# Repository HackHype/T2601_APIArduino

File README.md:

# T2601 — API Arduino
> Modular I/O expansion board based on the ATmega328PB.

---

## System Architecture

### 🟦 Main Board
_Mother board of the system — orchestrates the entire bus_

- Hosts a compact dev board (Teensy-style)
- **3 Mezzanine slots** for I/O interface cards
- **N System Mezzanine slots** for advanced modules
  - FRAM / RTC / MicroSD / ... modules
- Power management for the entire system

---

### 🟩 Extension Board
_Bus slave node — based on the ATmega328P_

- Microcontroller: **ATmega328P**
- **2 Mezzanine slots** for I/O
- **Chained UART** communication across all extension boards
- Programming via **Arduino as ISP**

---

### 🟨 Mezzanine Card
_swappable I/O interface module — 25 × 25 mm_

| Driver         | Type        | Typical Use                  |
|----------------|-------------|------------------------------|
| ULN2803        | Sink NPN    | Relays, inductive loads      |
| MIC2981        | Source PNP  | High-voltage loads           |
| MOSFET         | Switch      | Power loads                  |
| Voltage divider| Passive     | Analog input                 |
| Optocoupler    | Isolated    | Galvanic isolation           |

---

## Repository Structure
```
T2601_APIArduino/
├── hardware/
│   ├── main_board/        # Main board
│   ├── extension_board/   # ATmega328P extension board
│   └── mezzanine/         # I/O mezzanine cards
├── firmware/              # Arduino code
├── docs/                  # Schematics, datasheets
└── README.md
```

---

## License

This project is open hardware — **CERN OHL v2 Strongly Reciprocal**.

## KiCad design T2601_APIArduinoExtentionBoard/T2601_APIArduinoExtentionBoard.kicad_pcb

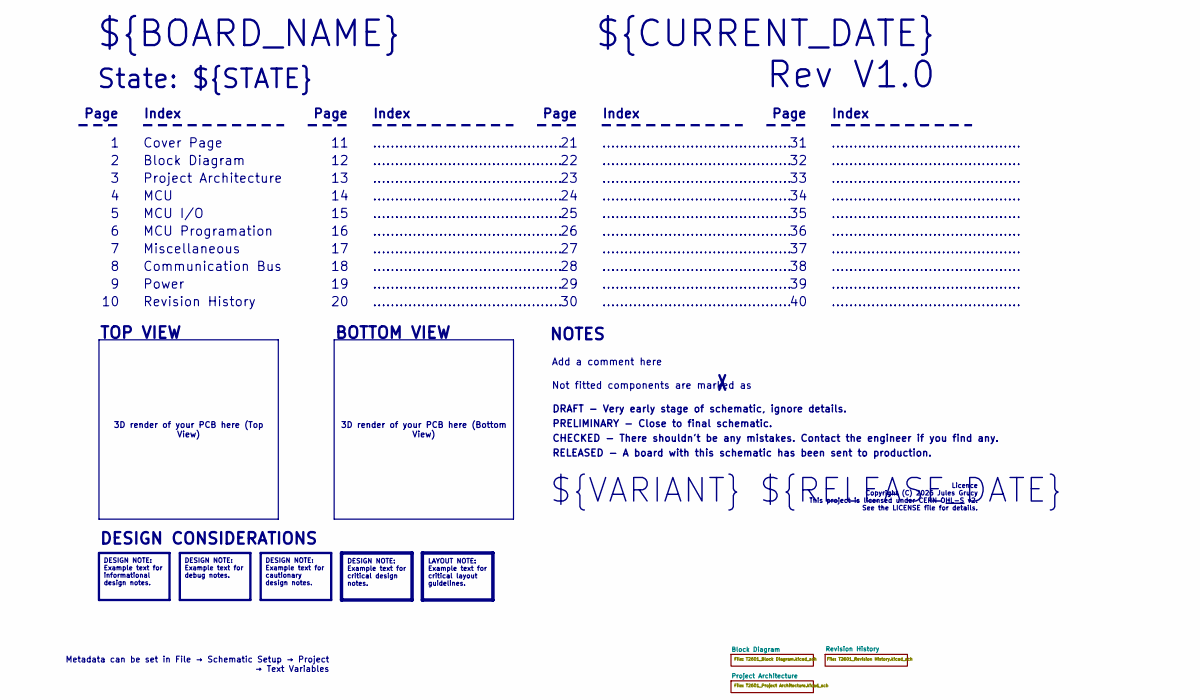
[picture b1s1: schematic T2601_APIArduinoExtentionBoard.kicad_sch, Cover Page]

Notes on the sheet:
BOTTOM VIEW
...........................................
RELEASED - A board with this schematic has been sent to production.
Page
TOP VIEW
Revision History
Power
Communication Bus
Not fitted components are marked as
Index
PRELIMINARY - Close to final schematic.
${VARIANT} ${RELEASE_DATE}
MCU
${CURRENT_DATE}
State: ${STATE}
Rev ${REVISION}
MCU I/O
${BOARD_NAME}
DRAFT - Very early stage of schematic, ignore details.
MCU Programation
Licence Copyright (C) 2026 Jules Grucy This project is licensed under CERN OHL-S v2. See the LICENSE file for details.
Block Diagram
Add a comment here
Cover Page
NOTES
Project Architecture
CHECKED - There shouldn't be any mistakes. Contact the engineer if you find any.
DESIGN CONSIDERATIONS
Miscellaneous
3D render of your PCB here (Bottom View)
3D render of your PCB here (Top View)
Metadata can be set in File → Schematic Setup → Project → Text Variables
DESIGN NOTE: Example text for informational design notes.
LAYOUT NOTE: Example text for critical layout guidelines.
DESIGN NOTE: Example text for cautionary design notes.
DESIGN NOTE: Example text for debug notes.
DESIGN NOTE: Example text for critical design notes.

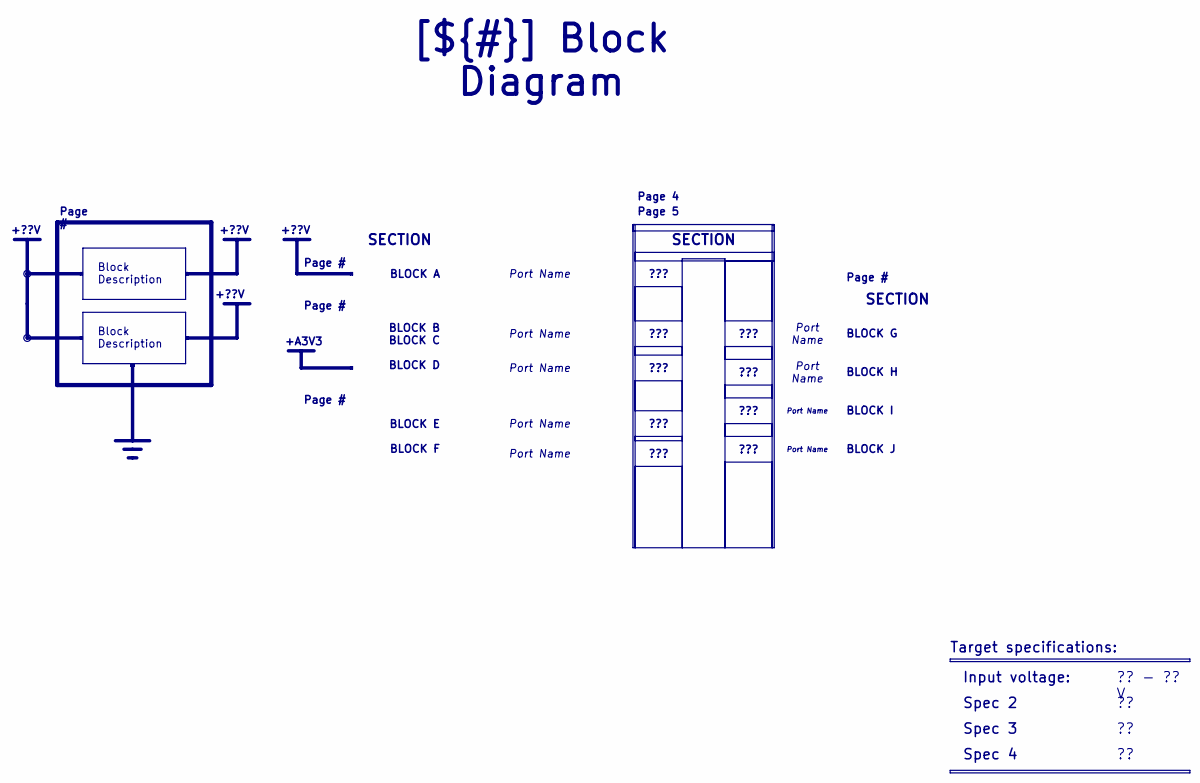
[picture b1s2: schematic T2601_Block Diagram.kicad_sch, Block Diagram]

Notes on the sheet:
+??V
+A3V3
Spec 3
Block Description
???
Spec 2
Port Name
SECTION
Page #
Input voltage:
BLOCK E BLOCK F
BLOCK A
BLOCK I
BLOCK G
[${#}] ${TITLE}
Target specifications:
?? - ?? V
Page 4
BLOCK J
Page 5
BLOCK B BLOCK C BLOCK D
Spec 4
BLOCK H

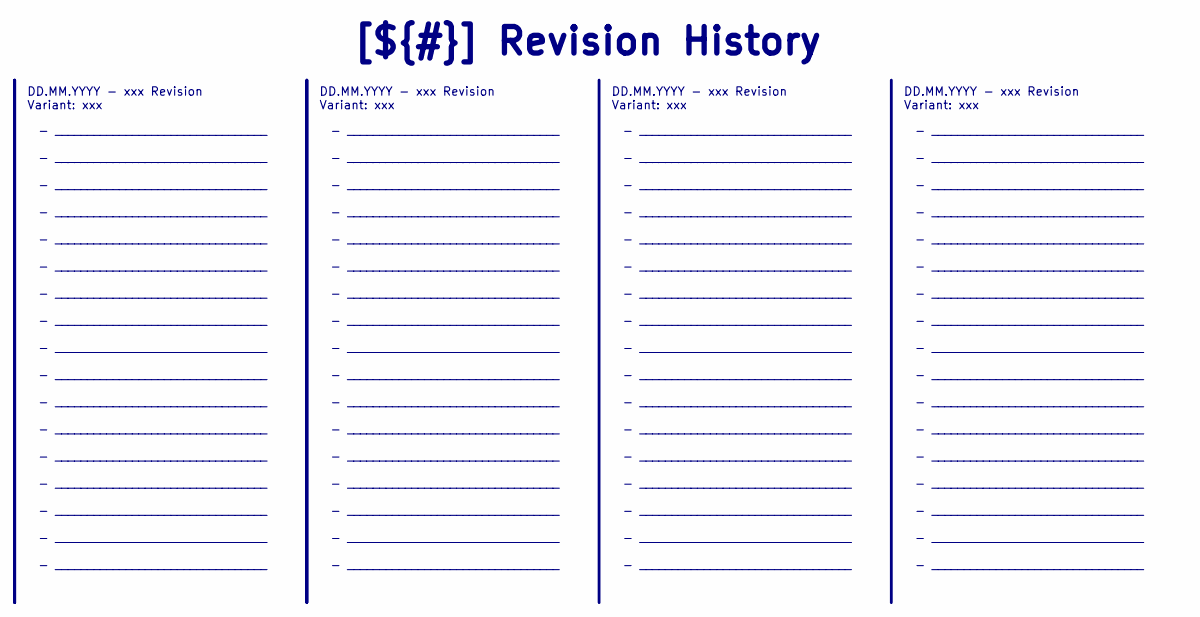
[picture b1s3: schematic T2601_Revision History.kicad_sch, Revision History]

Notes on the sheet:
- _________________________________ - _________________________________ - _________________________________ - _________________________________ - _________________________________ - _________________________________ - _________________________________ - _________________________________ - _________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
DD.MM.YYYY - xxx Revision Variant: xxx
[${#}] ${TITLE}

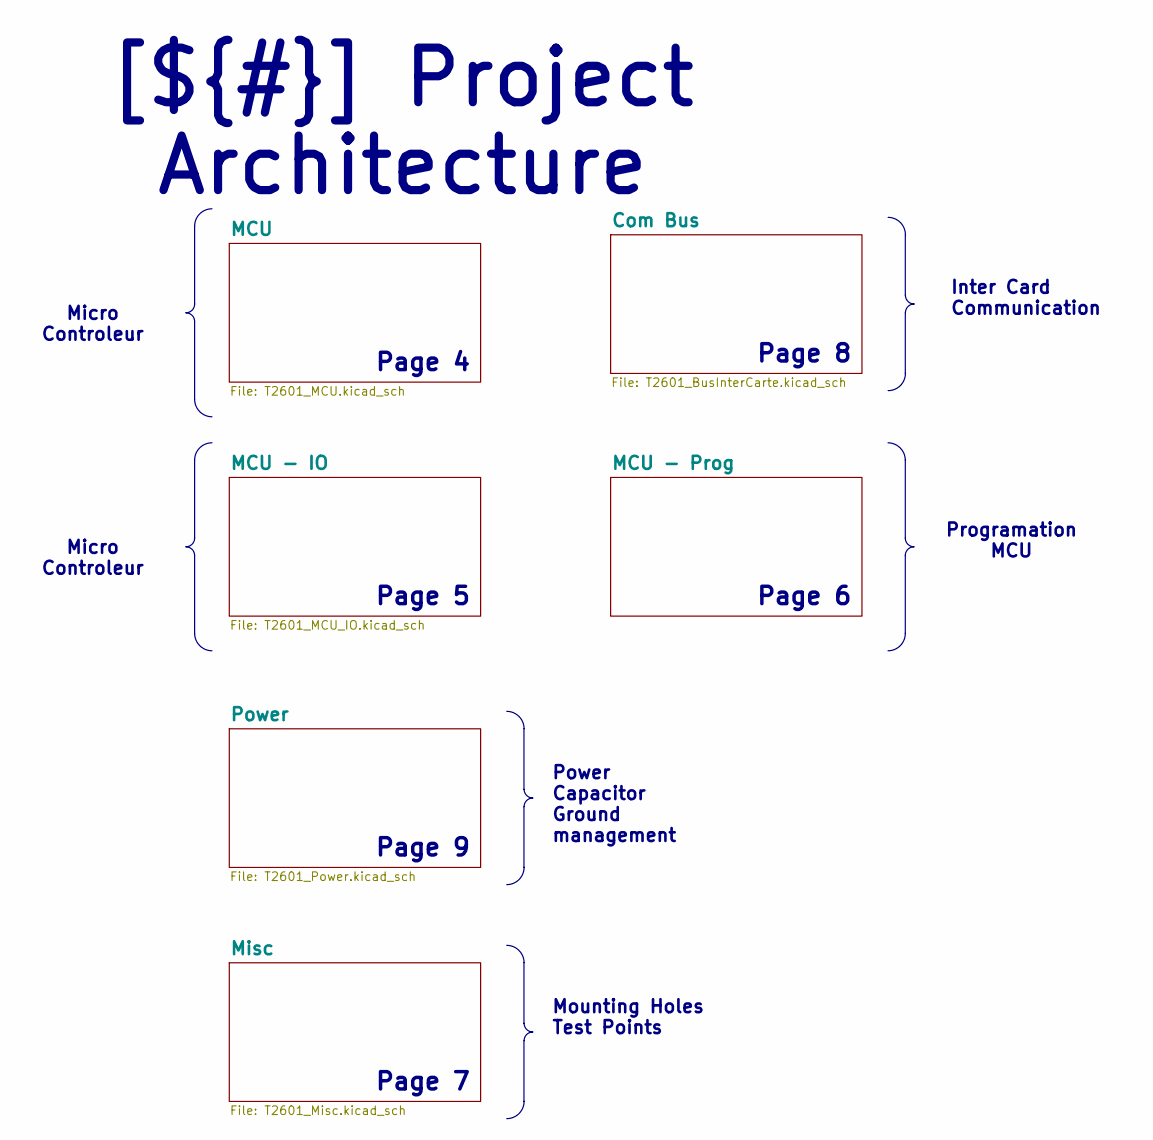
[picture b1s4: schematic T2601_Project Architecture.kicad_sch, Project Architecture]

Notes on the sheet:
Page 6
Page 8
Page 4
Page 5
Page 9
Page 7
Programation MCU
Micro Controleur
Inter Card Communication
[${#}] ${TITLE}
Power Capacitor Ground management
Mounting Holes Test Points

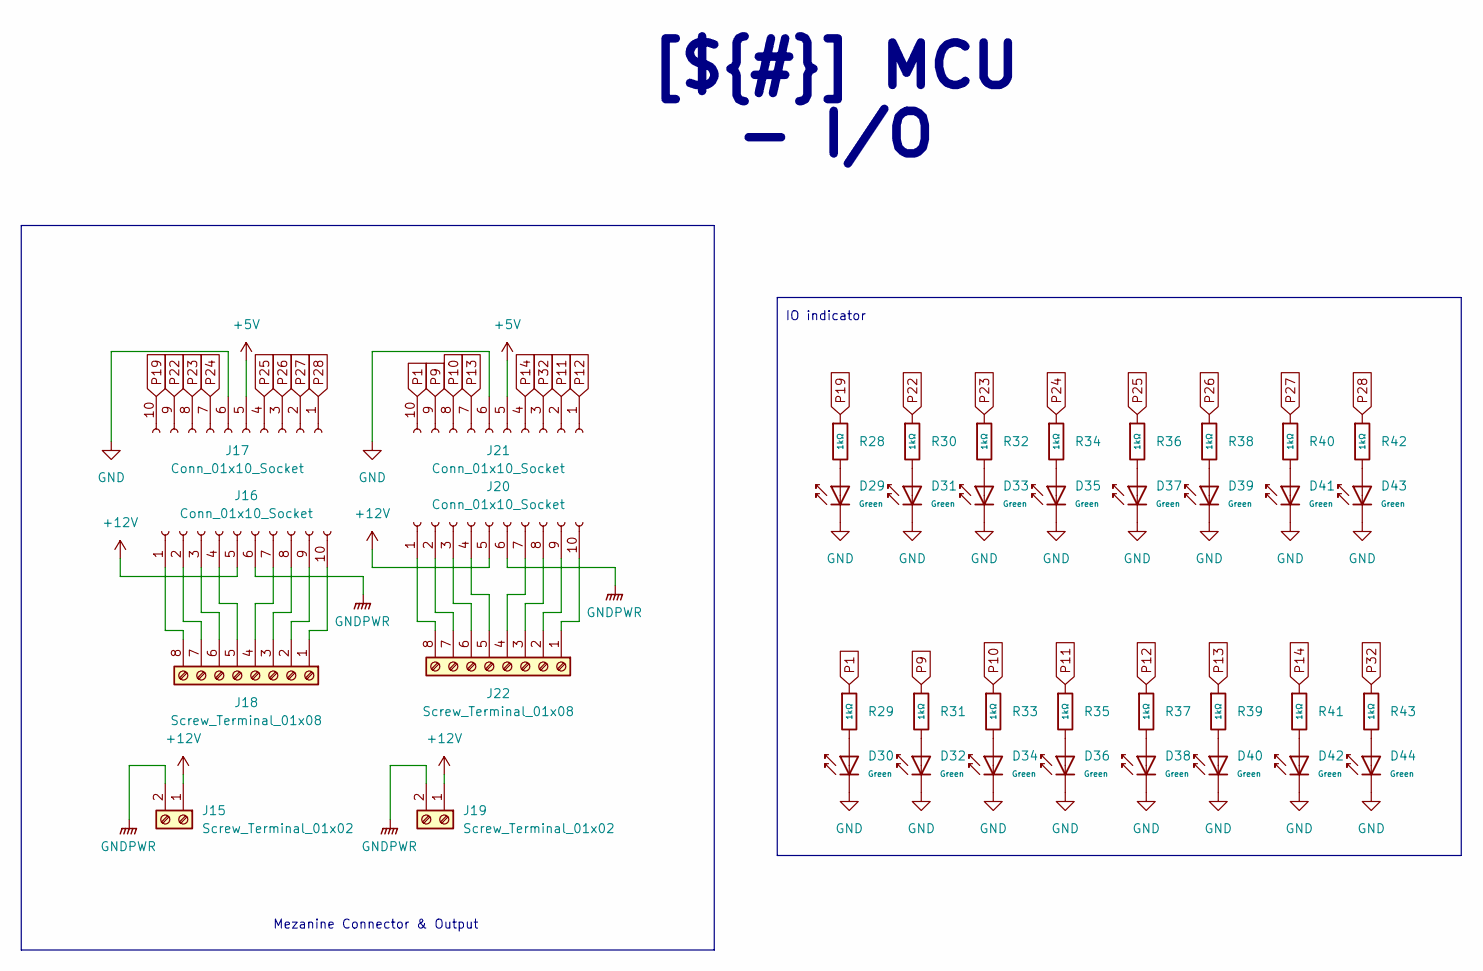
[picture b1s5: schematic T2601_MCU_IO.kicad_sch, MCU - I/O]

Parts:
D29, D30, D31, D32, D33, D34, D35, D36, D37, D38, D39, D40, D41, D42, D43, D44: Green; D_0805; Part KT-0805G; LCSC C2297
J15, J19: Screw_Terminal_01x02; TerminalBlock_Xinya_XY308-2.54-2P_1x02_P2.54mm_Horizontal
J16, J17, J20, J21: Conn_01x10_Socket; PinSocket_1x10_P2.54mm_Vertical
J18, J22: Screw_Terminal_01x08; TerminalBlock_TE_282834-8_1x08_P2.54mm_Horizontal
R28, R29, R30, R31, R32, R33, R34, R35, R36, R37, R38, R39, R40, R41, R42, R43: 1kΩ; R_0402; Overload Voltage (Max) 50V; Tolerance ±1%; Part 0402WGF1001TCE; LCSC C11702

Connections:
+5V: J17.5, J21.5; also elsewhere on the board
+12V: J15.1, J16.5, J19.1, J20.5; also elsewhere on the board
GND: D29.1, D30.1, D31.1, D32.1, D33.1, D34.1, D35.1, D36.1, D37.1, D38.1, D39.1, D40.1, D41.1, D42.1, D43.1, D44.1, J17.6, J21.6; also elsewhere on the board
GNDPWR: J15.2, J16.6, J19.2, J20.6; also elsewhere on the board
unnamed: D29.2, R28.2
unnamed: D30.2, R29.2
unnamed: D31.2, R30.2
unnamed: D32.2, R31.2
unnamed: D33.2, R32.2
unnamed: D34.2, R33.2
unnamed: D35.2, R34.2
unnamed: D36.2, R35.2
unnamed: D37.2, R36.2
unnamed: D38.2, R37.2
unnamed: D39.2, R38.2
unnamed: D40.2, R39.2
unnamed: D41.2, R40.2
unnamed: D42.2, R41.2
unnamed: D43.2, R42.2
unnamed: D44.2, R43.2
unnamed: J16.1, J18.8
unnamed: J16.2, J18.7
unnamed: J16.3, J18.6
unnamed: J16.4, J18.5
unnamed: J16.7, J18.4
unnamed: J16.8, J18.3
unnamed: J16.9, J18.2
unnamed: J16.10, J18.1
unnamed: J20.1, J22.8
unnamed: J20.2, J22.7
unnamed: J20.3, J22.6
unnamed: J20.4, J22.5
unnamed: J20.7, J22.4
unnamed: J20.8, J22.3
unnamed: J20.9, J22.2
unnamed: J20.10, J22.1
P1: J21.10, R29.1; also elsewhere on the board
P9: J21.9, R31.1; also elsewhere on the board
P10: J21.8, R33.1; also elsewhere on the board
P11: J21.2, R35.1; also elsewhere on the board
P12: J21.1, R37.1; also elsewhere on the board
P13: J21.7, R39.1; also elsewhere on the board
P14: J21.4, R41.1; also elsewhere on the board
P19: J17.10, R28.1; also elsewhere on the board
P22: J17.9, R30.1; also elsewhere on the board
P23: J17.8, R32.1; also elsewhere on the board
P24: J17.7, R34.1; also elsewhere on the board
P25: J17.4, R36.1; also elsewhere on the board
P26: J17.3, R38.1; also elsewhere on the board
P27: J17.2, R40.1; also elsewhere on the board
P28: J17.1, R42.1; also elsewhere on the board
P32: J21.3, R43.1; also elsewhere on the board

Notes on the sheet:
IO indicator
Mezanine Connector & Output
[${#}] ${TITLE}

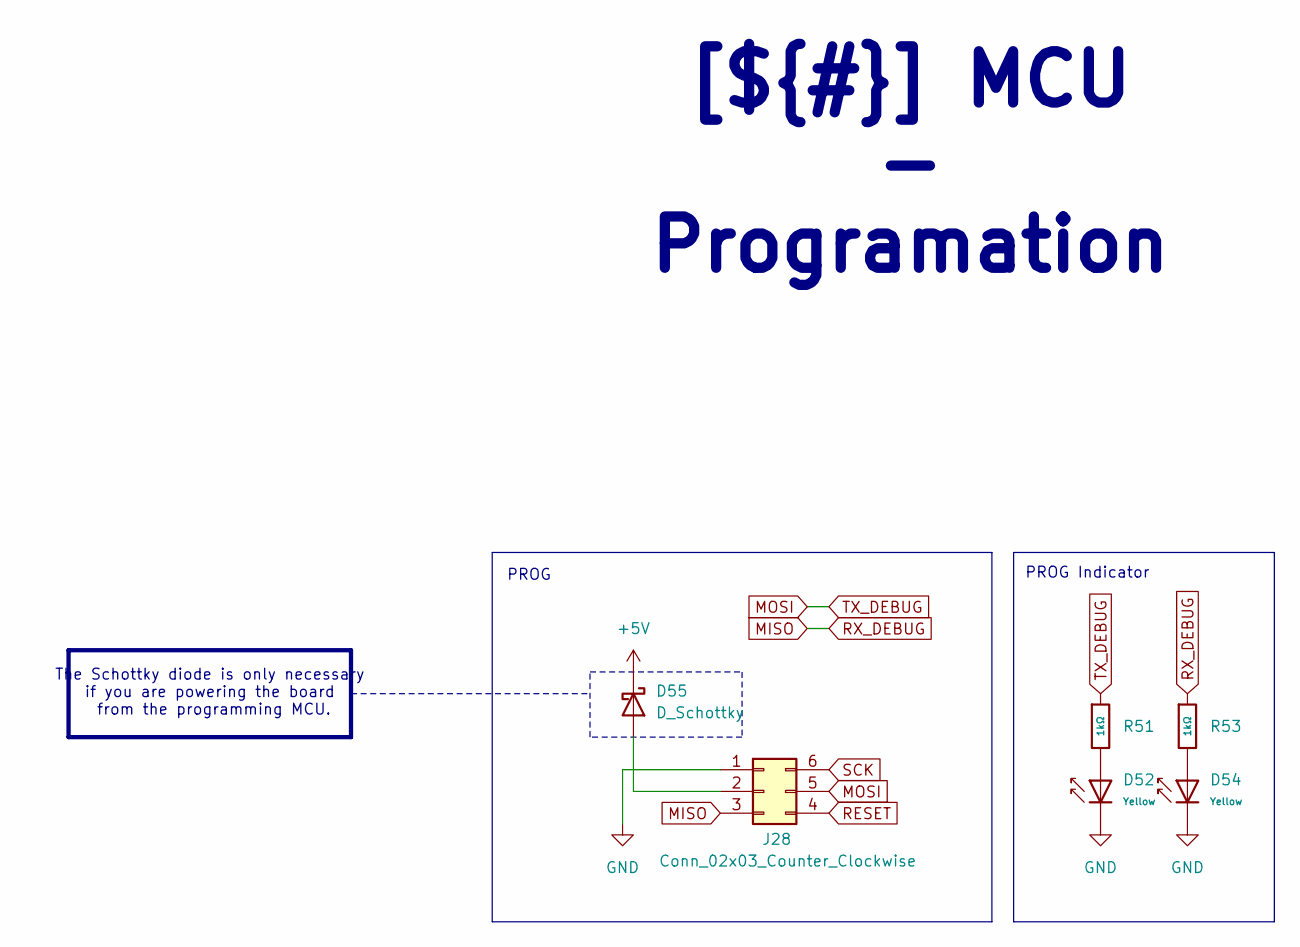
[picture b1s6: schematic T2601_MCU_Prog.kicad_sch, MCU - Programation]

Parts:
D52, D54: Yellow; D_0805; Part KT-0805Y; LCSC C2296
D55: D_Schottky; D_5W_P12.70mm_Horizontal
J28: Conn_02x03_Counter_Clockwise; PinSocket_2x03_P2.54mm_Vertical
R51, R53: 1kΩ; R_0402; Overload Voltage (Max) 50V; Tolerance ±1%; Part 0402WGF1001TCE; LCSC C11702

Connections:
+5V: D55.1 (K); also elsewhere on the board
GND: D52.1, D54.1, J28.1; also elsewhere on the board
MISO: J28.3, R53.1; also elsewhere on the board
MOSI: J28.5, R51.1; also elsewhere on the board
unnamed: D52.2, R51.2
unnamed: D54.2, R53.2
unnamed: D55.2 (A), J28.2
RESET: J28.4; also elsewhere on the board
SCK: J28.6; also elsewhere on the board

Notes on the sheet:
PROG Indicator
PROG
The Schottky diode is only necessary if you are powering the board from the programming MCU.
[${#}] ${TITLE}

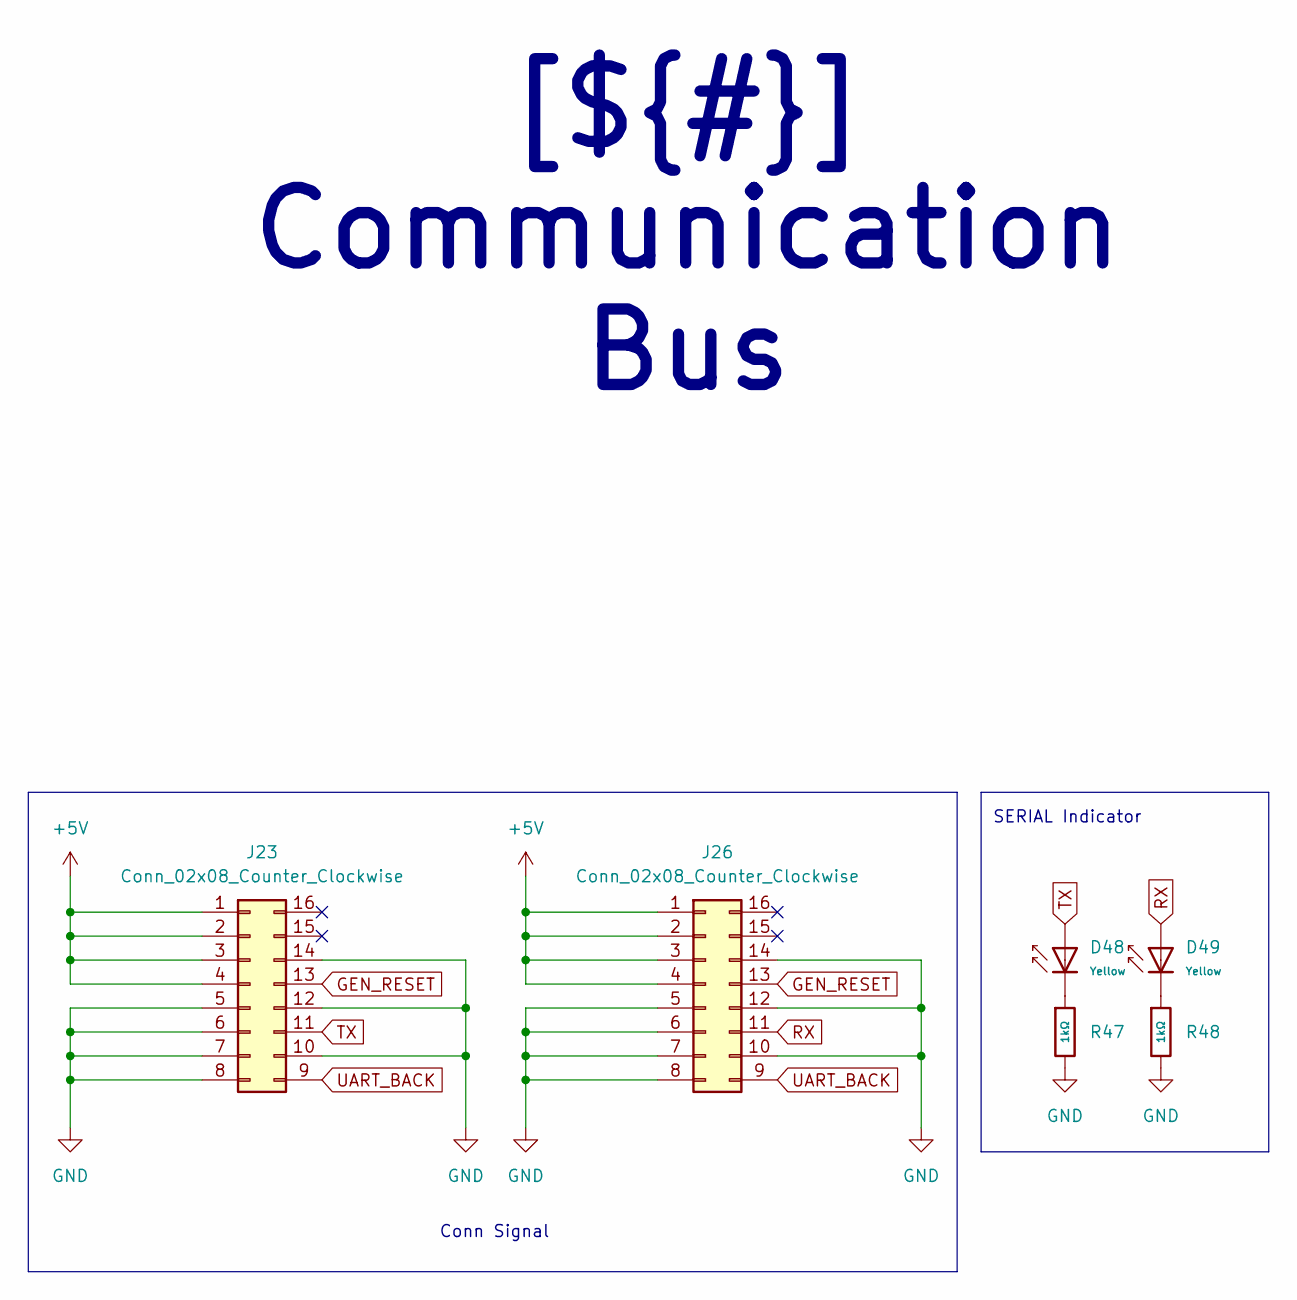
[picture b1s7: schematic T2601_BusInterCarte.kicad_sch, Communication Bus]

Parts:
D48, D49: Yellow; D_0805; Part KT-0805Y; LCSC C2296
J23, J26: Conn_02x08_Counter_Clockwise; IDC-Header_2x08_P2.54mm_Vertical
R47, R48: 1kΩ; R_0402; Overload Voltage (Max) 50V; Tolerance ±1%; Part 0402WGF1001TCE; LCSC C11702

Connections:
+5V: J23.1, J23.2, J23.3, J23.4, J26.1, J26.2, J26.3, J26.4; also elsewhere on the board
GEN_RESET: J23.13, J26.13; also elsewhere on the board
GND: J23.5, J23.6, J23.7, J23.8, J23.10, J23.12, J23.14, J26.5, J26.6, J26.7, J26.8, J26.10, J26.12, J26.14, R47.2, R48.2; also elsewhere on the board
unnamed: D48.1, R47.1
unnamed: D49.1, R48.1
RX: D49.2, J26.11; also elsewhere on the board
TX: D48.2, J23.11; also elsewhere on the board
UART_BACK: J23.9, J26.9

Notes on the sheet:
Conn Signal
SERIAL Indicator
[${#}] ${TITLE}

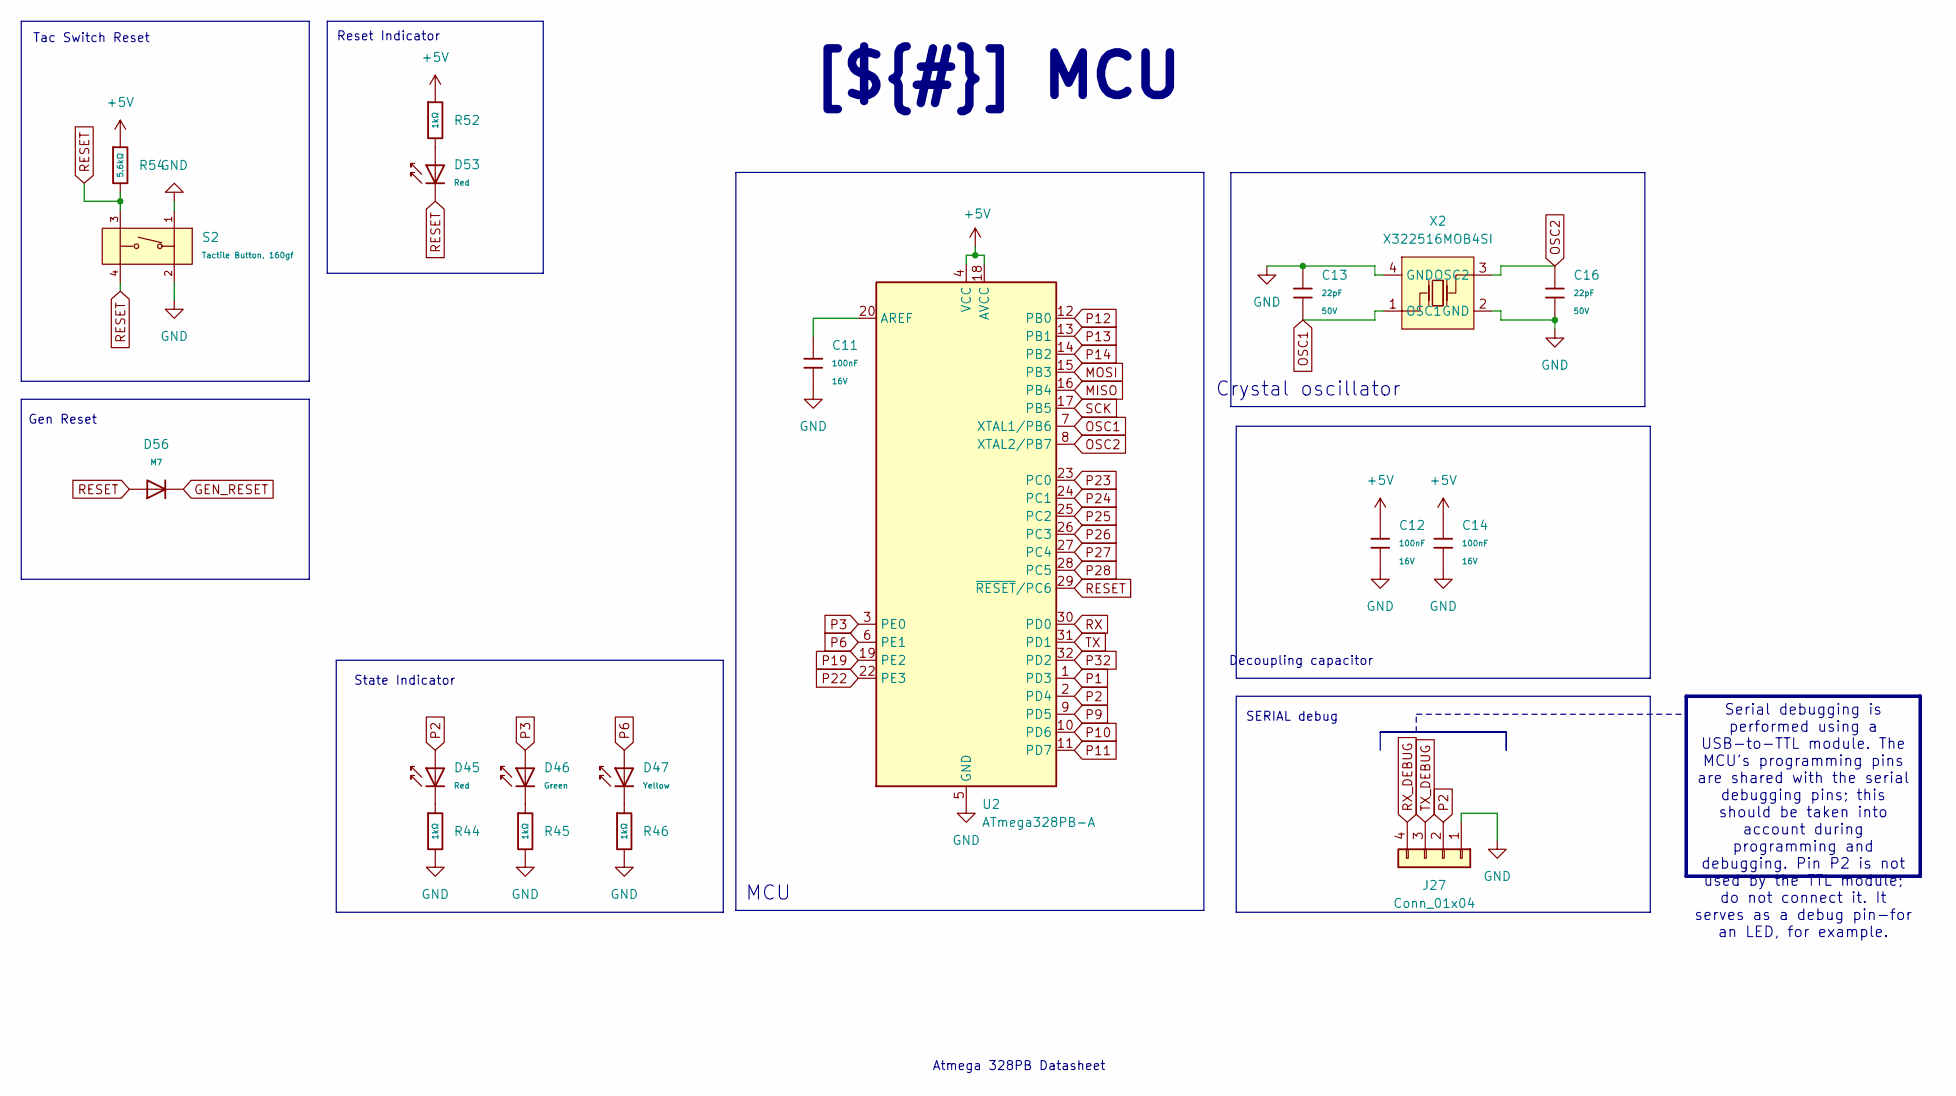
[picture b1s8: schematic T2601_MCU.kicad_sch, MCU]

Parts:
C11, C12, C14: 100nF; C_0402; Voltage Rated 16V; Tolerance ±10%; Part CL05B104KO5NNNC; LCSC C1525
C13, C16: 22pF; C_0402; Voltage Rated 50V; Tolerance ±5%; Part 0402CG220J500NT; LCSC C1555
D45, D53: Red; D_0805; Forward Voltage (VF) 1.6V~2.6V; Part NCD0805R1; LCSC C84256
D46: Green; D_0805; Part KT-0805G; LCSC C2297
D47: Yellow; D_0805; Part KT-0805Y; LCSC C2296
D56: M7; D_SMA; Forward Voltage (Vf@If) 1.1V@1A; Reverse Voltage (Vr) 1kV; Part M7; LCSC C95872
J27: Conn_01x04; PinSocket_1x04_P2.54mm_Vertical
R44, R45, R46, R52: 1kΩ; R_0402; Overload Voltage (Max) 50V; Tolerance ±1%; Part 0402WGF1001TCE; LCSC C11702
R54: 5.6kΩ; R_0603; Overload Voltage (Max) 75V; Tolerance ±1%; Part 0603WAF5601T5E; LCSC C23189
S2: Tactile Button, 160gf; SW-SMD_4P-L5.1-W5.1-P3.70-LS6.5-TL-2; Voltage Rating (Dc) 12V; Part TS-1187A-B-A-B; LCSC C318884
U2: ATmega328PB-A; TQFP-32_7x7mm_P0.8mm
X2: X322516MOB4SI; CRYSTAL-SMD_4P-L3.2-W2.5-BL; LCSC Part C12668

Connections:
+5V: C12.1, C14.1, R52.1, R54.1, U2.4 (VCC), U2.18 (AVCC); also elsewhere on the board
GEN_RESET: D56.1; also elsewhere on the board
GND: C11.2, C12.2, C13.1, C14.2, C16.2, J27.1, R44.2, R45.2, R46.2, S2.1 (A), S2.2 (B), U2.5 (GND), U2.21 (GND), X2.2 (GND), X2.4 (GND); also elsewhere on the board
MISO: J27.4, U2.16 (PB4); also elsewhere on the board
MOSI: J27.3, U2.15 (PB3); also elsewhere on the board
unnamed: D45.1, R44.1
unnamed: D46.1, R45.1
unnamed: D47.1, R46.1
unnamed: D53.2, R52.2
unnamed: C11.1, U2.20 (AREF)
OSC1: C13.2, U2.7 (XTAL1/PB6), X2.1 (OSC1)
OSC2: C16.1, U2.8 (XTAL2/PB7), X2.3 (OSC2)
P1: U2.1 (PD3); also elsewhere on the board
P2: D45.2, J27.2, U2.2 (PD4)
P3: D46.2, U2.3 (PE0)
P6: D47.2, U2.6 (PE1)
P9: U2.9 (PD5); also elsewhere on the board
P10: U2.10 (PD6); also elsewhere on the board
P11: U2.11 (PD7); also elsewhere on the board
P12: U2.12 (PB0); also elsewhere on the board
P13: U2.13 (PB1); also elsewhere on the board
P14: U2.14 (PB2); also elsewhere on the board
P19: U2.19 (PE2); also elsewhere on the board
P22: U2.22 (PE3); also elsewhere on the board
P23: U2.23 (PC0); also elsewhere on the board
P24: U2.24 (PC1); also elsewhere on the board
P25: U2.25 (PC2); also elsewhere on the board
P26: U2.26 (PC3); also elsewhere on the board
P27: U2.27 (PC4); also elsewhere on the board
P28: U2.28 (PC5); also elsewhere on the board
P32: U2.32 (PD2); also elsewhere on the board
RESET: D53.1, D56.2, R54.2, S2.3 (C), S2.4 (D), U2.29 (~RESET/PC6); also elsewhere on the board
RX: U2.30 (PD0); also elsewhere on the board
SCK: U2.17 (PB5); also elsewhere on the board
TX: U2.31 (PD1); also elsewhere on the board

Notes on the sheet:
State Indicator
Decoupling capacitor
Tac Switch Reset
Gen Reset
MCU
SERIAL debug
Atmega 328PB Datasheet
Crystal oscillator
Reset Indicator
Serial debugging is performed using a USB-to-TTL module. The MCU's programming pins are shared with the serial debugging pins; this should be taken into account during programming and debugging. Pin P2 is not used by the TTL module; do not connect it. It serves as a debug pin-for an LED, for exampl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
[${#}] ${TITLE}

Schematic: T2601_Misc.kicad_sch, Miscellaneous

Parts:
H1, H2, H3, H4: MountingHole; MountingHole_3.2mm_M3
TP1, TP2, TP3: TestPoint; TestPoint_Loop_D2.50mm_Drill1.0mm_LowProfile

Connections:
+5V: TP3.1 (1_1); also elsewhere on the board
+12V: TP2.1 (1_1); also elsewhere on the board
GND: TP1.1 (1_1); also elsewhere on the board

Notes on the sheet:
[${#}] ${TITLE}

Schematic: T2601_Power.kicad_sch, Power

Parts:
C9, C10: C; C_Radial_D6.3mm_H11.0mm_P2.50mm
D50, D51: Green; D_0805; Part KT-0805G; LCSC C2297
J24, J25: Conn_01x04_Pin; JST_XH_B4B-XH-A_1x04_P2.50mm_Vertical
JP13, JP14, JP16, JP17, JP18, JP20, JP21, JP22, JP24: SolderJumper_2_Open; SolderJumper-2_P1.3mm_Open_RoundedPad1.0x1.5mm
R49: 2.4kΩ; R_0603; Overload Voltage (Max) 75V; Tolerance ±1%; Part 0603WAF2401T5E; LCSC C22940
R50: 1kΩ; R_0603; Overload Voltage (Max) 75V; Tolerance ±1%; Part 0603WAF1001T5E; LCSC C21190

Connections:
+5V: C9.1, C10.1, R50.1; also elsewhere on the board
+12V: J24.3, J24.4, J25.3, J25.4, R49.1; also elsewhere on the board
GND: C9.2, C10.2, D51.1, JP13.1 (A), JP14.1 (A), JP16.1 (A), JP17.1 (A), JP18.1 (A), JP20.1 (A), JP21.1 (A), JP22.1 (A), JP24.1 (A); also elsewhere on the board
GNDPWR: D50.1, J24.1, J24.2, J25.1, J25.2, JP13.2 (B), JP14.2 (B), JP16.2 (B), JP17.2 (B), JP18.2 (B), JP20.2 (B), JP21.2 (B), JP22.2 (B), JP24.2 (B); also elsewhere on the board
unnamed: D50.2, R49.2
unnamed: D51.2, R50.2

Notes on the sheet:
PWR Indicator
Conn PWR
[${#}] ${TITLE}

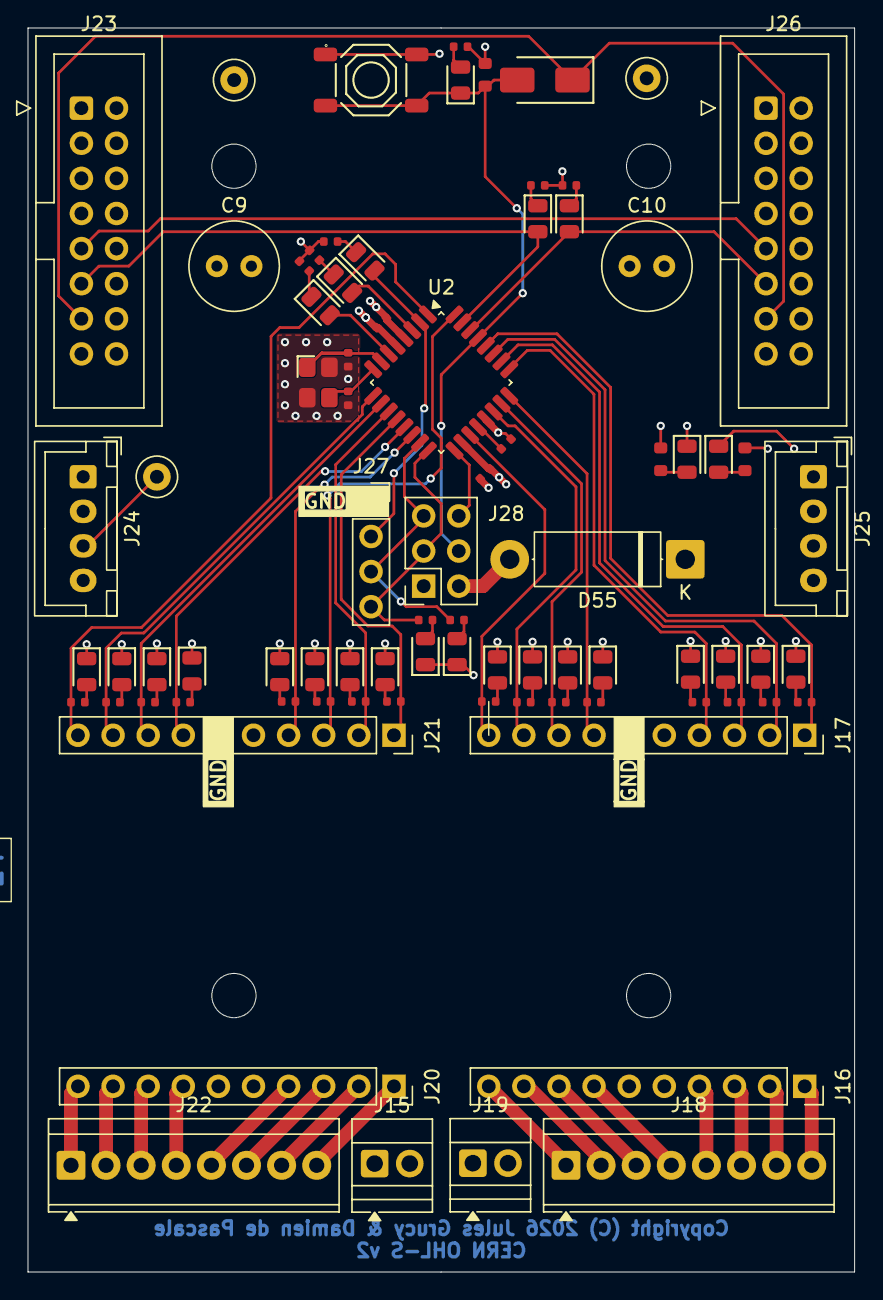
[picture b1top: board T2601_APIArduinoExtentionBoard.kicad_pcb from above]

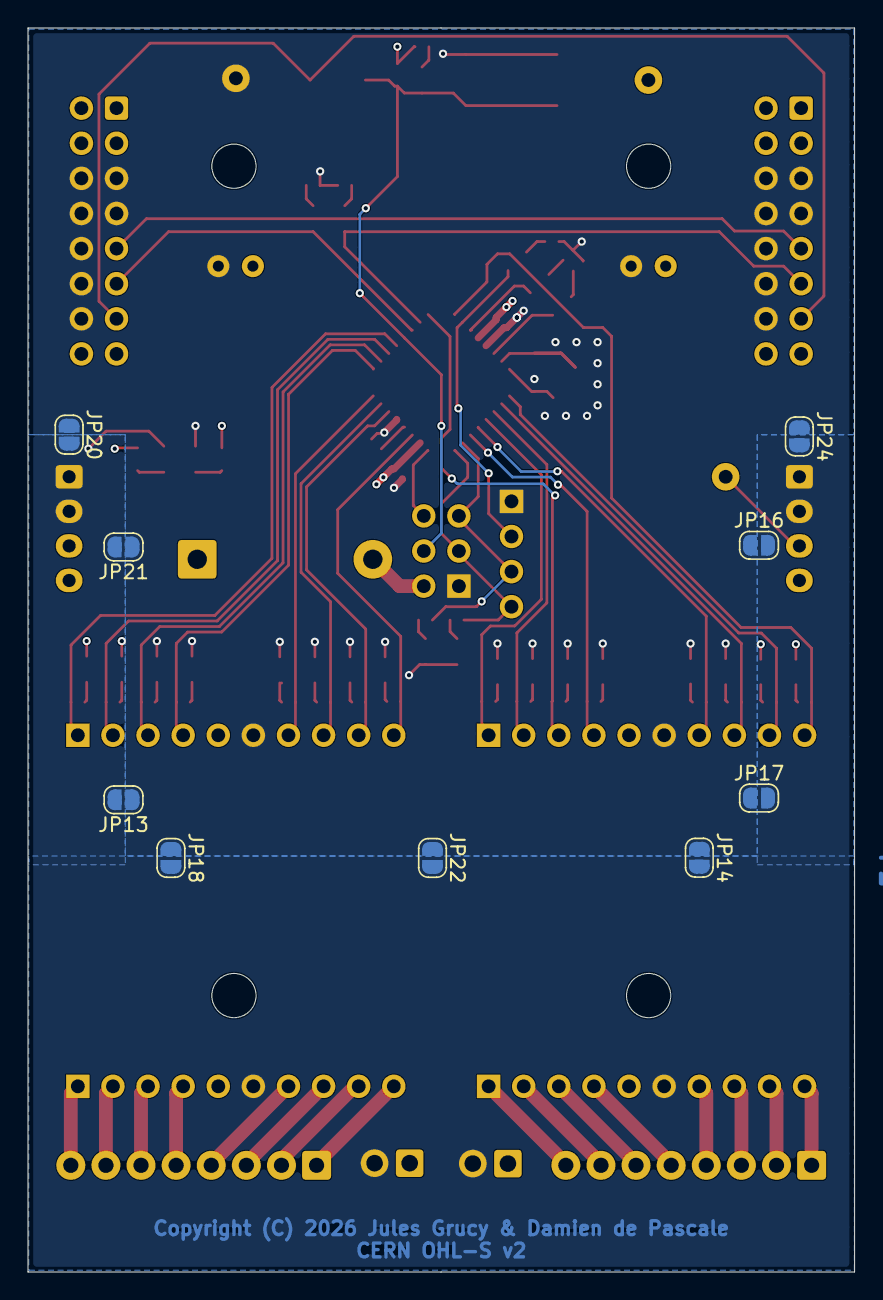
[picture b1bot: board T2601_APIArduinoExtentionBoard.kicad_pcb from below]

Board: 4 copper layers, 59.8 x 90.0 mm, 95 parts (9 on the bottom side), 77 nets.

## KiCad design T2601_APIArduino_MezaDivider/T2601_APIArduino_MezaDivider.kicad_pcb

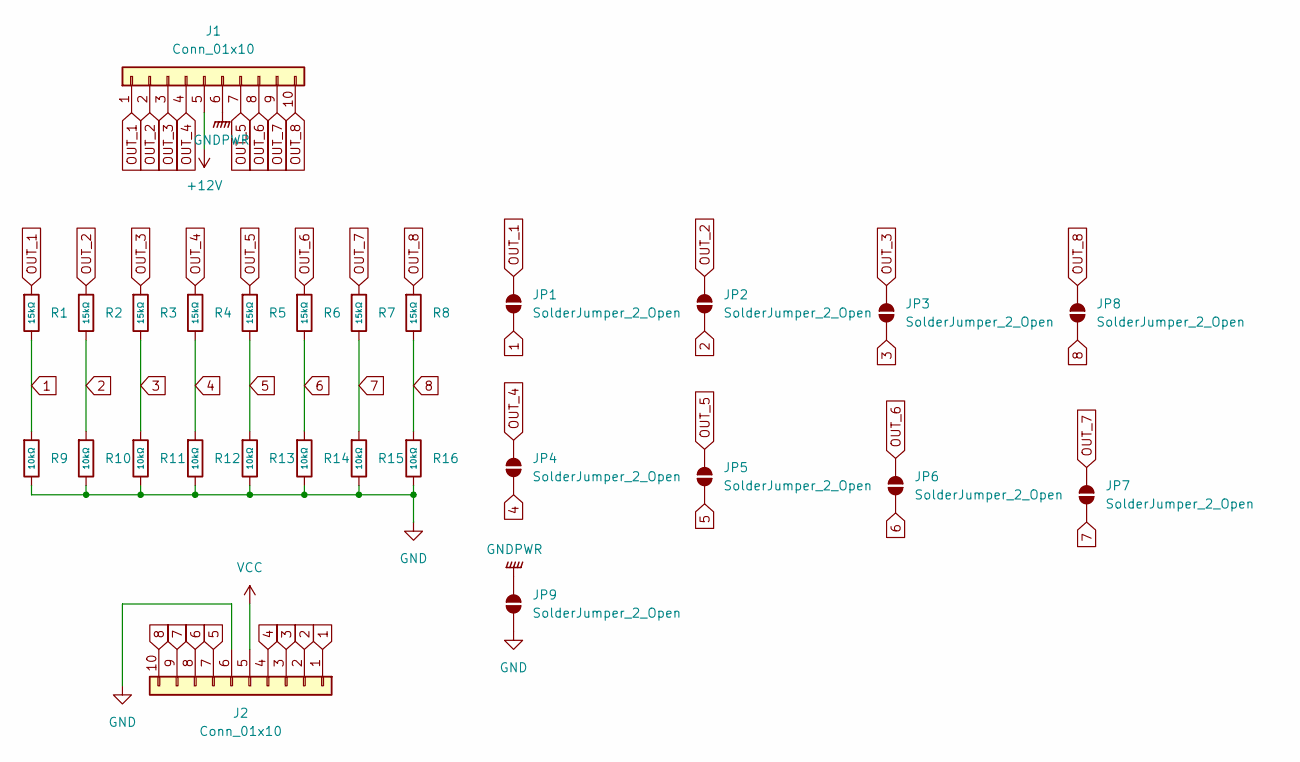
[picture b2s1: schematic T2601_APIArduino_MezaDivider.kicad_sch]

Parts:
J1, J2: Conn_01x10; PinHeader_1x10_P2.54mm_Vertical
JP1, JP2, JP3, JP4, JP5, JP6, JP7, JP8, JP9: SolderJumper_2_Open; SolderJumper-2_P1.3mm_Open_RoundedPad1.0x1.5mm
R1, R2, R3, R4, R5, R6, R7, R8: 15kΩ; R_0402; Overload Voltage (Max) 50V; Tolerance ±1%; Part 0402WGF1502TCE; LCSC C25756
R9, R10, R11, R12, R13, R14, R15, R16: 10kΩ; R_0402; Overload Voltage (Max) 50V; Tolerance ±1%; Part 0402WGF1002TCE; LCSC C25744

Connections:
1: J2.1, JP1.1 (A), R1.2, R9.1
2: J2.2, JP2.1 (A), R2.2, R10.1
3: J2.3, JP3.1 (A), R3.2, R11.1
4: J2.4, JP4.1 (A), R4.2, R12.1
5: J2.7, JP5.1 (A), R5.2, R13.1
6: J2.8, JP6.1 (A), R6.2, R14.1
7: J2.9, JP7.1 (A), R7.2, R15.1
8: J2.10, JP8.1 (A), R8.2, R16.1
+12V: J1.5
GND: J2.6, JP9.1 (A), R9.2, R10.2, R11.2, R12.2, R13.2, R14.2, R15.2, R16.2
GNDPWR: J1.6, JP9.2 (B)
OUT_1: J1.1, JP1.2 (B), R1.1
OUT_2: J1.2, JP2.2 (B), R2.1
OUT_3: J1.3, JP3.2 (B), R3.1
OUT_4: J1.4, JP4.2 (B), R4.1
OUT_5: J1.7, JP5.2 (B), R5.1
OUT_6: J1.8, JP6.2 (B), R6.1
OUT_7: J1.9, JP7.2 (B), R7.1
OUT_8: J1.10, JP8.2 (B), R8.1
VCC: J2.5

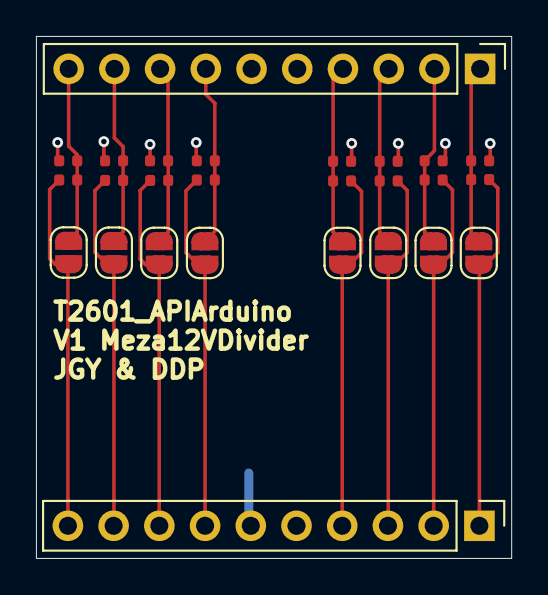
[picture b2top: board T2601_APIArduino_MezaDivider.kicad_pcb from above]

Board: 2 copper layers, 26.4 x 29.0 mm, 27 parts (1 on the bottom side), 18 nets.

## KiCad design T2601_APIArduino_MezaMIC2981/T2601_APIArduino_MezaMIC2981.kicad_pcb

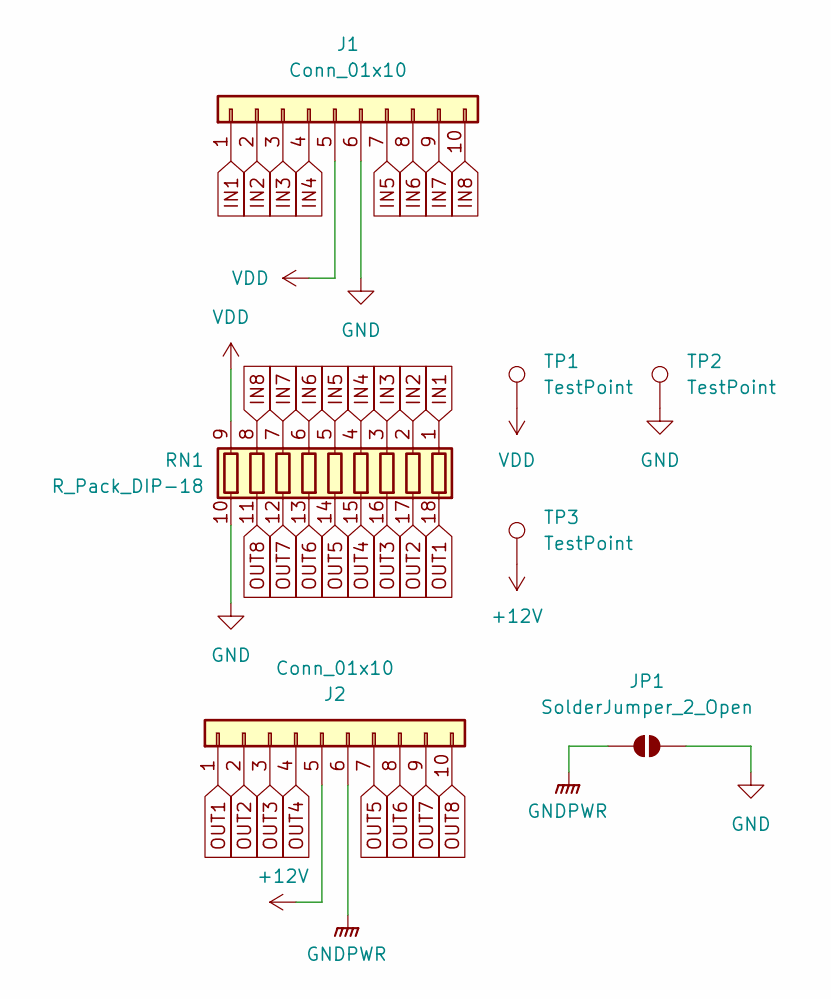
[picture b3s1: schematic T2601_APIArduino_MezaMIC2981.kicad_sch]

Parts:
J1, J2: Conn_01x10; PinHeader_1x10_P2.54mm_Vertical
JP1: SolderJumper_2_Open; SolderJumper-2_P1.3mm_Open_RoundedPad1.0x1.5mm
RN1: R_Pack_DIP-18; DIP-18_W7.62mm_Socket_LongPads
TP1, TP2, TP3: TestPoint; TestPoint_Pad_D1.5mm

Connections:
+12V: J2.5, TP3.1
GND: J1.6, JP1.2 (B), RN1.10 (R9.2), TP2.1
GNDPWR: J2.6, JP1.1 (A)
IN1: J1.1, RN1.1 (R1.1)
IN2: J1.2, RN1.2 (R2.1)
IN3: J1.3, RN1.3 (R3.1)
IN4: J1.4, RN1.4 (R4.1)
IN5: J1.7, RN1.5 (R5.1)
IN6: J1.8, RN1.6 (R6.1)
IN7: J1.9, RN1.7 (R7.1)
IN8: J1.10, RN1.8 (R8.1)
OUT1: J2.1, RN1.18 (R1.2)
OUT2: J2.2, RN1.17 (R2.2)
OUT3: J2.3, RN1.16 (R3.2)
OUT4: J2.4, RN1.15 (R4.2)
OUT5: J2.7, RN1.14 (R5.2)
OUT6: J2.8, RN1.13 (R6.2)
OUT7: J2.9, RN1.12 (R7.2)
OUT8: J2.10, RN1.11 (R8.2)
VDD: J1.5, RN1.9 (R9.1), TP1.1

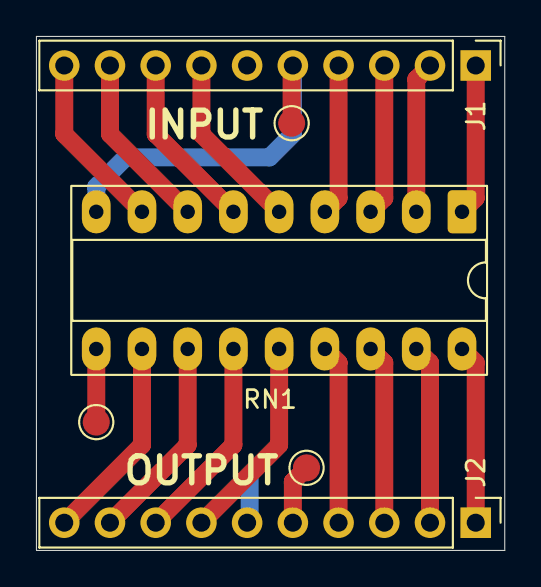
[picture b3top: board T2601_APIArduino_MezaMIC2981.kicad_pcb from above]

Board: 2 copper layers, 26.0 x 28.6 mm, 7 parts (1 on the bottom side), 20 nets.

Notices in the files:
README.md:
License: CERN OHL v2
T2601_APIArduinoExtentionBoard/T2601_APIArduinoExtentionBoard.kicad_pcb:
Copyright (C) 2026 Jules Grucy & Damien de Pascale
CERN OHL-S v2
